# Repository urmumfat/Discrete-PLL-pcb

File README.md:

# Discrete-PLL-pcb

Electronics project featuring a **Discrete Phase-Locked Loop (PLL)**.

### pcb photos and renders:
<div style="display: flex; gap: 10px;">

</div>

<div style="display: flex; gap: 10px;">

</div>

### pcb layout:
<div style="display: flex; gap: 10px;">

</div>

<div style="display: flex; gap: 10px;">

</div>

### circuit diagram:
<div style="display: flex; gap: 10px;">
  
</div>

## Project Scope
* **Design:** Analog-digital schematic and custom PCB layout in **KiCad**.
* **Hardware:** Discrete architecture utilizing **CD4030B** XOR gates and **TL074** op-amps.
* **Assembly:** Hand-soldered board featuring **BC846/857** transistor pairs.

## Repository Structure
* `/KiCad-files` – Schematic and PCB source files.
* `/gerbers` – Manufacturing data (Gerber and Drill files).
* `/images` – PCB renders, schematic exports, and project photos.
* `schematic.pdf` – Full circuit diagram.

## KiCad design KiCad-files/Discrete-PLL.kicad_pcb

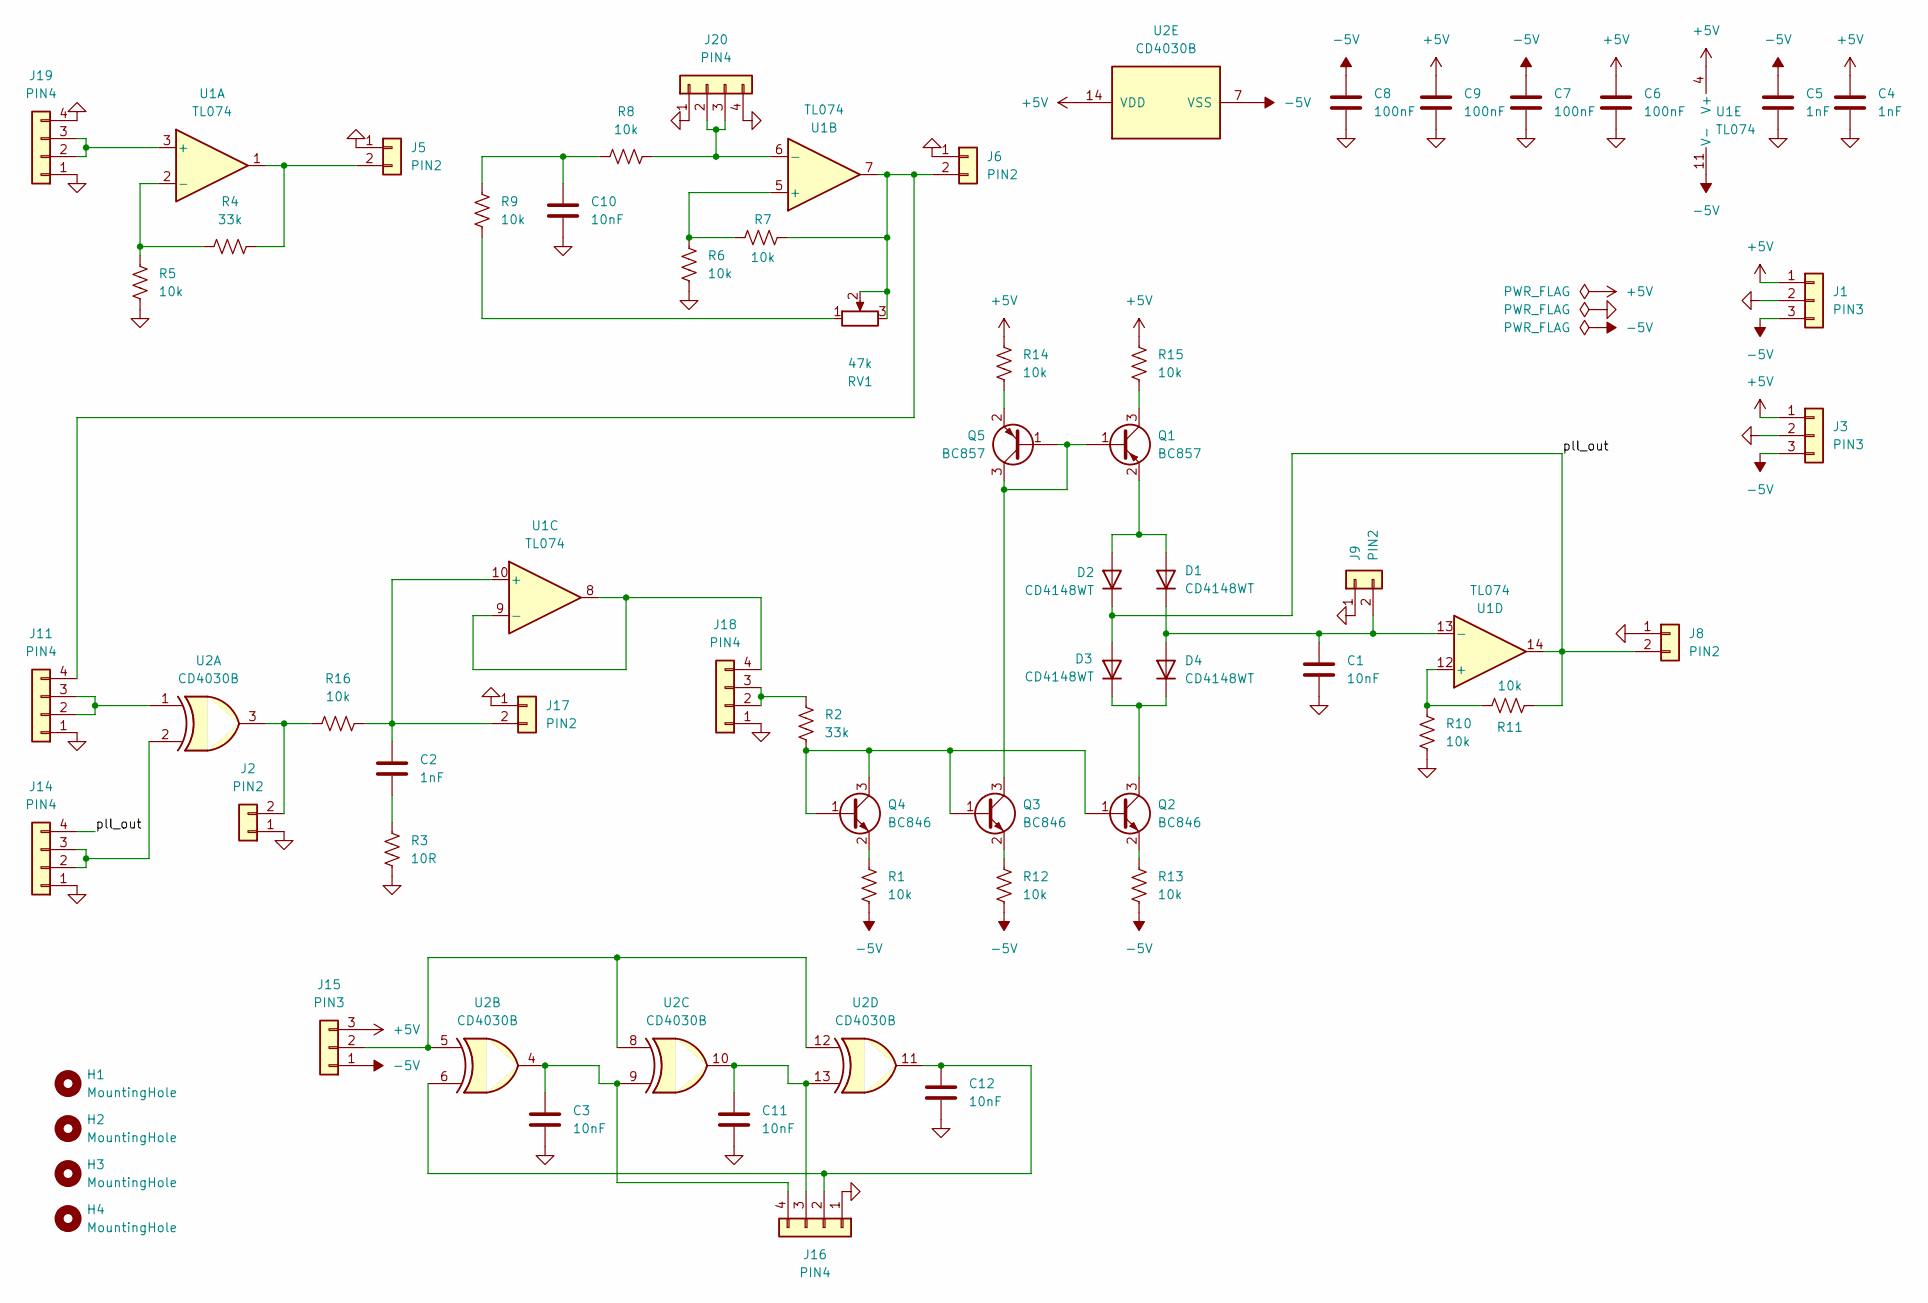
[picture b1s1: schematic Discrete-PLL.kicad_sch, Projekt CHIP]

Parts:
C1, C3, C10, C11, C12: 10nF; C_0603_1608Metric
C2, C4, C5: 1nF; C_0603_1608Metric
C6, C7, C8, C9: 100nF; C_0603_1608Metric
D1, D2, D3, D4: CD4148WT; D_0603_1608Metric_Pad1.05x0.95mm_HandSolder
H1, H2, H3, H4: MountingHole; MountingHole_3.2mm_M3_DIN965
J1, J3, J15: PIN3; PinHeader_1x03_P2.54mm_Vertical
J2, J5, J6, J8, J9, J17: PIN2; PinHeader_1x02_P2.54mm_Vertical
J11, J14, J16, J18, J19, J20: PIN4; PinHeader_1x04_P2.54mm_Vertical
Q1, Q5: BC857; SOT-23
Q2, Q3, Q4: BC846; SOT-23
R1, R5, R6, R7, R8, R9, R10, R11, R12, R13, R14, R15, R16: 10k; R_0603_1608Metric
R2, R4: 33k; R_0603_1608Metric
R3: 10R; R_0603_1608Metric
RV1: 47k; Potentiometer_CAP_CA14_VA12,5_Vertical
U1: TL074; SOIC-14_3.9x8.7mm_P1.27mm
U2: CD4030B; SOIC-14_3.9x8.7mm_P1.27mm

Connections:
+5V: C4.1, C6.1, C9.1, J1.1, J3.1, J15.3, R14.2, R15.2, U1.4 (V+), U2.14 (VDD)
-5V: C5.1, C7.1, C8.1, J1.3, J3.3, J15.1, R1.1, R12.1, R13.1, U1.11 (V-), U2.7 (VSS)
/pll_out: D2.1 (K), D3.2 (A), J8.2, J14.4, R11.2, U1.14
GND: C1.2, C3.2, C4.2, C5.2, C6.2, C7.2, C8.2, C9.2, C10.2, C11.2, C12.2, J1.2, J2.1, J3.2, J5.1, J6.1, J8.1, J9.1, J11.1, J14.1, J16.1, J17.1, J18.1, J19.1, J19.4, J20.1, J20.4, R3.1, R5.1, R6.1, R10.1
unnamed: C2.2, R3.2
unnamed: C10.1, R8.1, R9.2
unnamed: D1.2 (A), D2.2 (A), Q1.2 (E)
unnamed: C1.1, D1.1 (K), D4.2 (A), J9.2, U1.13 (-)
unnamed: D3.1 (K), D4.1 (K), Q2.3 (C)
unnamed: J2.2, R16.1, U2.3
unnamed: J5.2, R4.2, U1.1
unnamed: J11.2, J11.3, U2.1
unnamed: J6.2, J11.4, R7.2, RV1.2, RV1.3, U1.7
unnamed: J14.2, J14.3, U2.2
unnamed: J15.2, U2.5, U2.8, U2.12
unnamed: C12.1, J16.2, U2.6, U2.11
unnamed: C11.1, J16.3, U2.10, U2.13
unnamed: C3.1, J16.4, U2.4, U2.9
unnamed: C2.1, J17.2, R16.2, U1.10 (+)
unnamed: J18.2, J18.3, R2.2
unnamed: J18.4, U1.8, U1.9 (-)
unnamed: J19.2, J19.3, U1.3 (+)
unnamed: J20.2, J20.3, R8.2, U1.6 (-)
unnamed: Q1.1 (B), Q3.3 (C), Q5.1 (B), Q5.3 (C)
unnamed: Q1.3 (C), R15.1
unnamed: Q2.1 (B), Q3.1 (B), Q4.1 (B), Q4.3 (C), R2.1
unnamed: Q2.2 (E), R13.2
unnamed: Q3.2 (E), R12.2
unnamed: Q4.2 (E), R1.2
unnamed: Q5.2 (E), R14.1
unnamed: R9.1, RV1.1
unnamed: R4.1, R5.2, U1.2 (-)
unnamed: R6.2, R7.1, U1.5 (+)
unnamed: R10.2, R11.1, U1.12 (+)

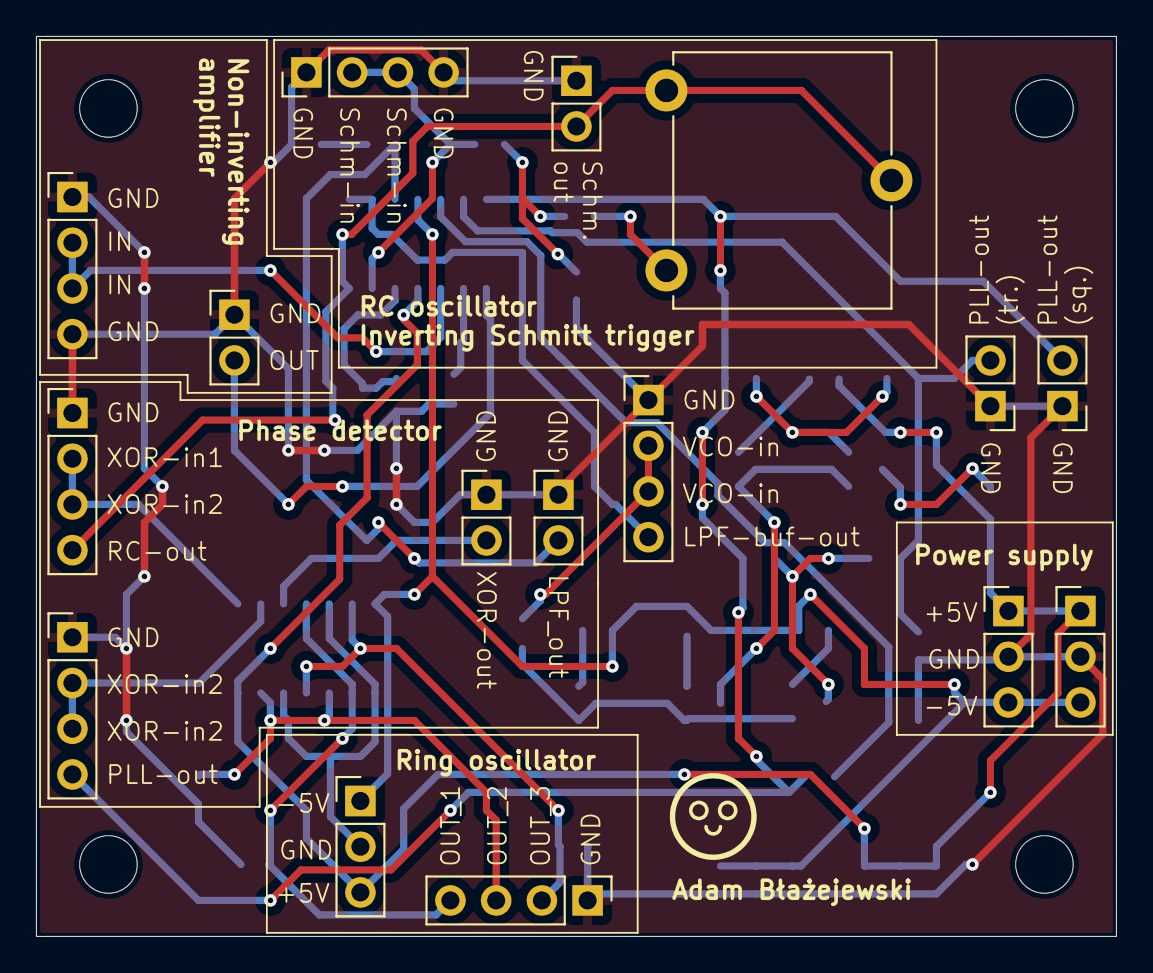
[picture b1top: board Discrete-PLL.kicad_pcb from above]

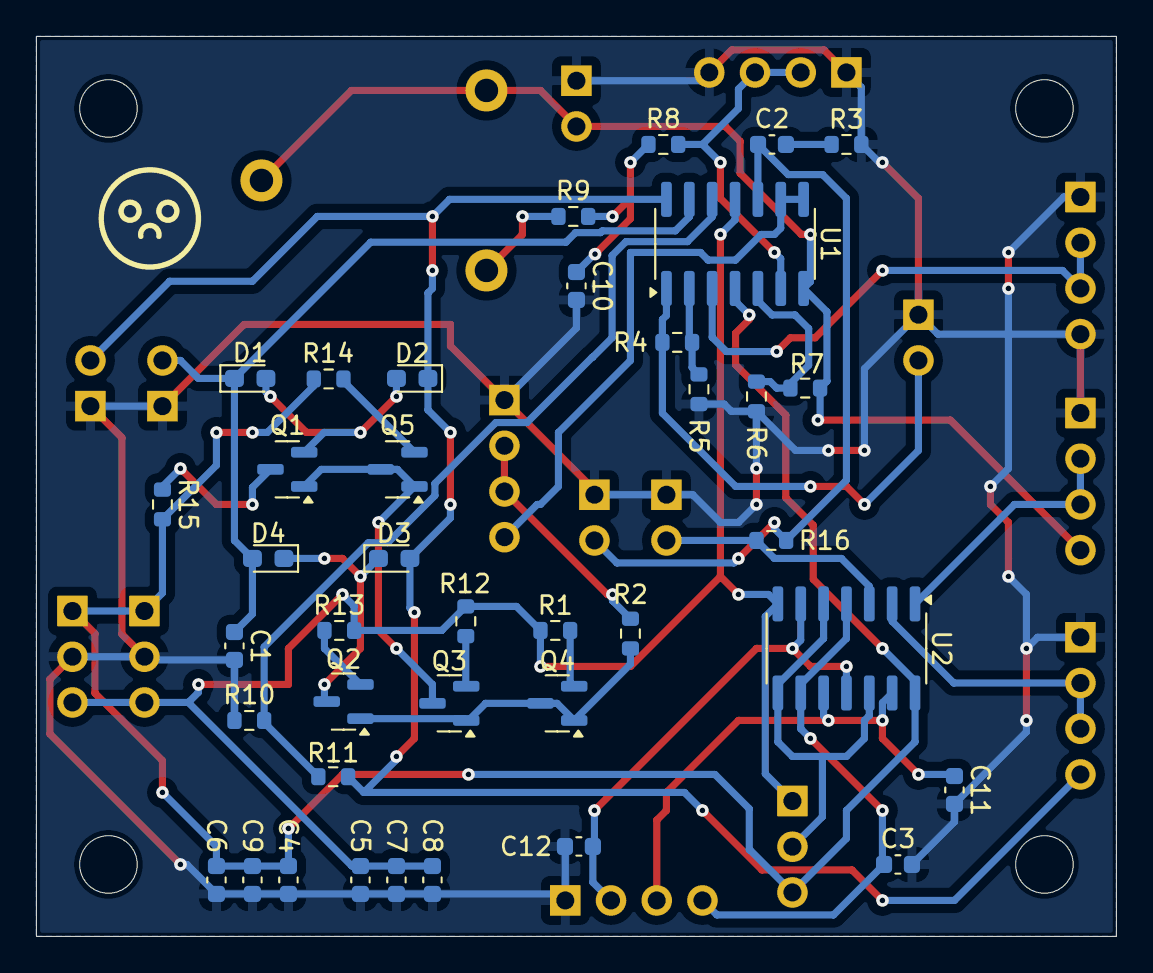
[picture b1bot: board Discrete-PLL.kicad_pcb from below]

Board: 2 copper layers, 60.0 x 50.0 mm, 59 parts (39 on the bottom side), 34 nets.

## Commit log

2026-04-02 added gerber files
2026-04-02 added KiCad files
2026-04-03 photos added
2026-04-03 added schematics
2026-04-04 pcb and schematics images added
2026-04-05 readme update
2026-04-05 readme source fix
2026-04-05 readme redraft
